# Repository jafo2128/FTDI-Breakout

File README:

FTDI-Breakout
-------------
USB to Serial Adapter with FTDI FT232R
http://www.watterott.com/en/FTDI-Breakout-Reloaded-V11

Features:
 * 3V3 and 5V compatible (switch)
 * Overcurrent protection (resettable polyswitch fuse)
 * Standard 6 pin FTDI connector (for Arduino)
 * Standard 4 pin Prop Plug connector (for Parallax Propeller and Basic-Stamps)

Directories:
 /pcb - Schematics and Layout files

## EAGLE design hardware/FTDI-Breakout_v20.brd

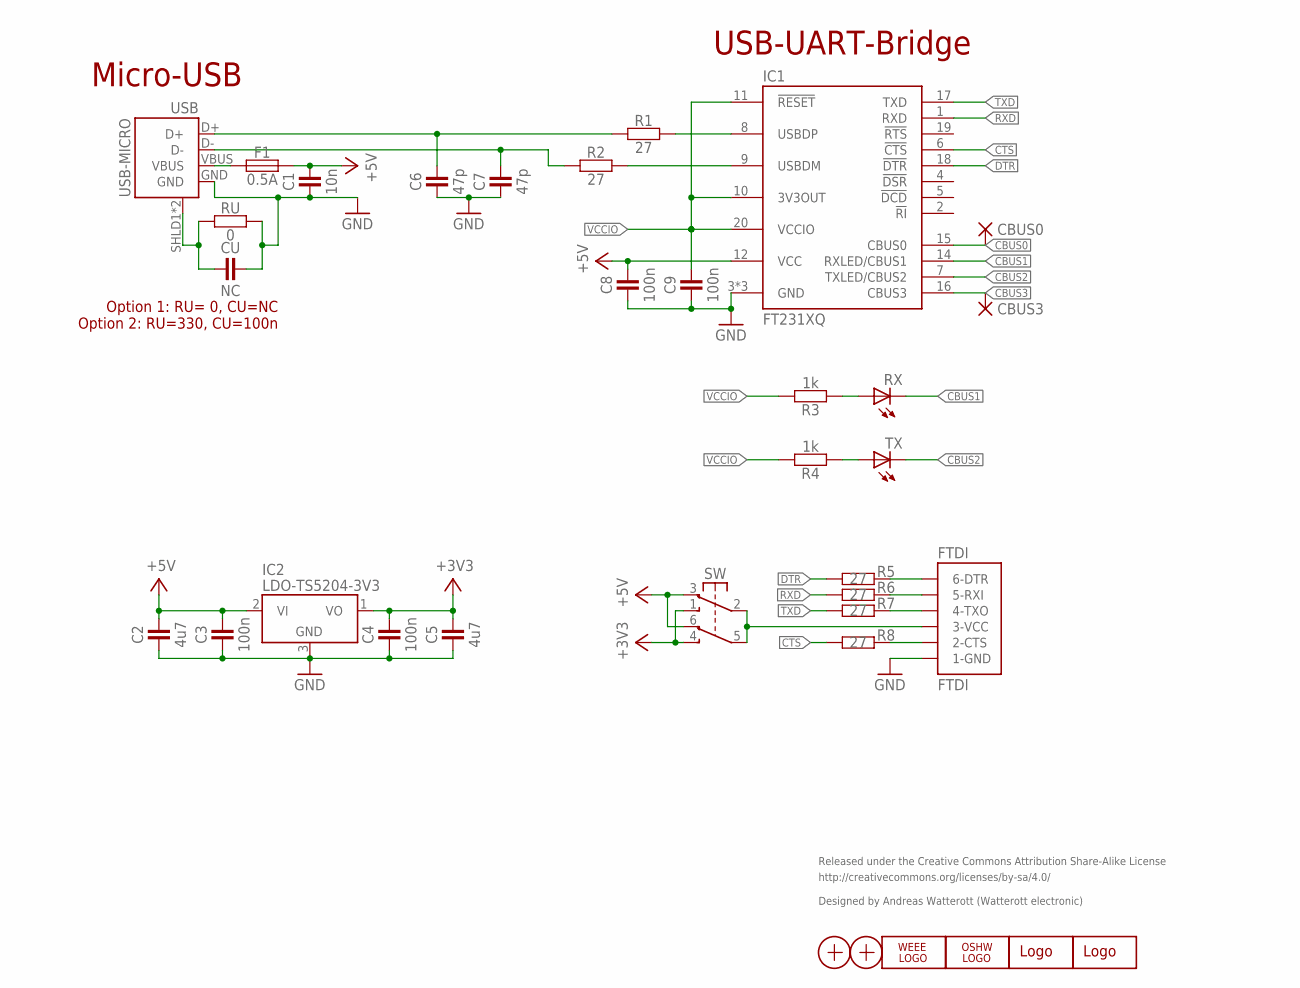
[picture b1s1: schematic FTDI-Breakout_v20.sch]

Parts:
C1: 10n; C0603
C2, C5: 4u7; C0805
C3, C4, C8, C9: 100n; C0603
C6, C7: 47p; C0603
CBUS0, CBUS3: PAD-1.27X1.27_NC
CU: NC; C0603
F1: 0.5A; C0805
FTDI: FTDI
IC1: FT231XQ; QFN20-PAD
IC2: LDO-TS5204-3V3; SOT23
LOGO1: WEEE_LOGO-S; WEEE_TPLAC_S
LOGO2: OSHW_LOGOX0070; OSHW_6X70
LOGO3: LOGO-S_PLACE_S; SPARK_TPLACE_S
LOGO4: LOGO-S_PLACE_M; SPARK_TPLACE_M
R1, R2, R5, R6, R7, R8: 27; C0603
R3, R4: 1k; C0603
RU: 0; C0603
RX: LED-0603; C0603
SW: SW-2UM-CUS22B; SW_CUS22B
TX: LED-0603; C0603
USB: USB-MICRO; USB-MICRO-10103594
X1, X2: PASSER-07; PASSER_07MM

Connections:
+3V3: C4.2, C5.2, IC2.1 (VO), SW.1 (S1), SW.4 (S2)
+5V: C1.2, C2.2, C3.2, C8.2, F1.2, IC1.12 (VCC), IC2.2 (VI), SW.3 (O1), SW.6 (O2)
CBUS0: CBUS0.1, IC1.15 (CBUS0)
CBUS1: IC1.14 (RXLED/CBUS1), RX.C
CBUS2: IC1.7 (TXLED/CBUS2), TX.C
CBUS3: CBUS3.1, IC1.16 (CBUS3)
CTS: IC1.6 (!CTS), R8.1
D2_N: IC1.9 (USBDM), R2.2
D2_P: IC1.8 (USBDP), R1.2
DTR: IC1.18 (!DTR), R5.1
D_N: C7.2, R2.1, USB.D-
D_P: C6.2, R1.1, USB.D+
FTDI-CTS: FTDI.2-CTS, R8.2
FTDI-DTR: FTDI.6-DTR, R5.2
FTDI-RXI: FTDI.5-RX (5-RXI), R6.2
FTDI-TXO: FTDI.4-TX (4-TXO), R7.2
FTDI-VCC: FTDI.3-VCC, SW.2 (P1), SW.5 (P2)
GND: C1.1, C2.1, C3.1, C4.1, C5.1, C6.1, C7.1, C8.1, C9.1, CU.2, FTDI.1-GND, IC1.3 (GND), IC1.13 (GND), IC1.TP (GND), IC2.3 (GND), RU.2, USB.GND
unnamed: CU.1, RU.1, USB.SHLD1 (SHIELD), USB.SHLD2 (SHIELD)
RX-LED: R3.1, RX.A
RXD: IC1.1 (RXD), R6.1
TX-LED: R4.1, TX.A
TXD: IC1.17 (TXD), R7.1
VBUS: F1.1, USB.VBUS
VCCIO: C9.2, IC1.10 (3V3OUT), IC1.11 (!RESET), IC1.20 (VCCIO), R3.2, R4.2

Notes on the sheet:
Released under the Creative Commons Attribution Share-Alike License
http://creativecommons.org/licenses/by-sa/4.0/
Designed by Andreas Watterott (Watterott electronic)
Option 1: RU= 0, CU=NC Option 2: RU=330, CU=100n
USB-UART-Bridge
Micro-USB

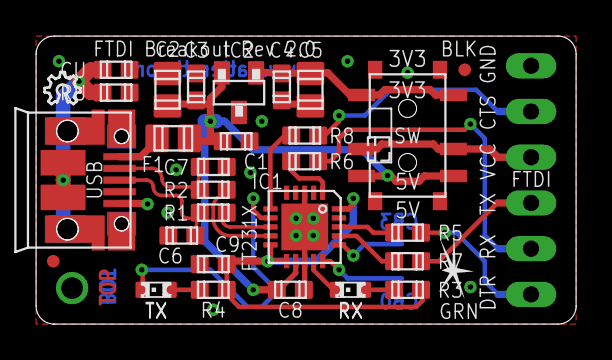
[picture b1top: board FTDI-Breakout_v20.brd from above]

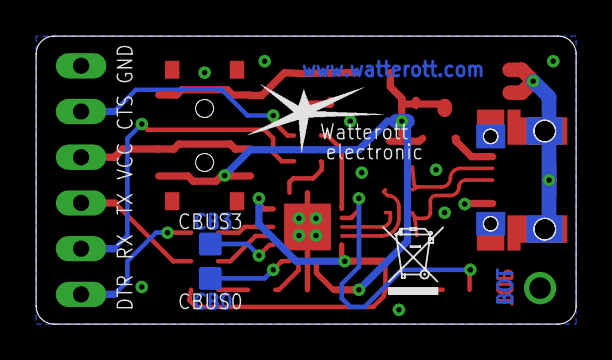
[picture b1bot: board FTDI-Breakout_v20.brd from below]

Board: 2 copper layers, 30.0 x 16.0 mm, 35 parts (4 on the bottom side), 25 nets.

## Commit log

2012-03-10 added layout files
2012-03-10 updated docu
2012-03-11 added license information
2013-01-21 updated image
2013-08-01 updated pcb
2014-03-10 updated license infos
2014-11-06 added v2 layout and schematics
2014-11-06 updated schematics and layout
2014-12-12 cleaned up schematics and layout
2015-01-10 moved image
2015-05-08 updated layout and schematics
2015-08-21 changed path structure
